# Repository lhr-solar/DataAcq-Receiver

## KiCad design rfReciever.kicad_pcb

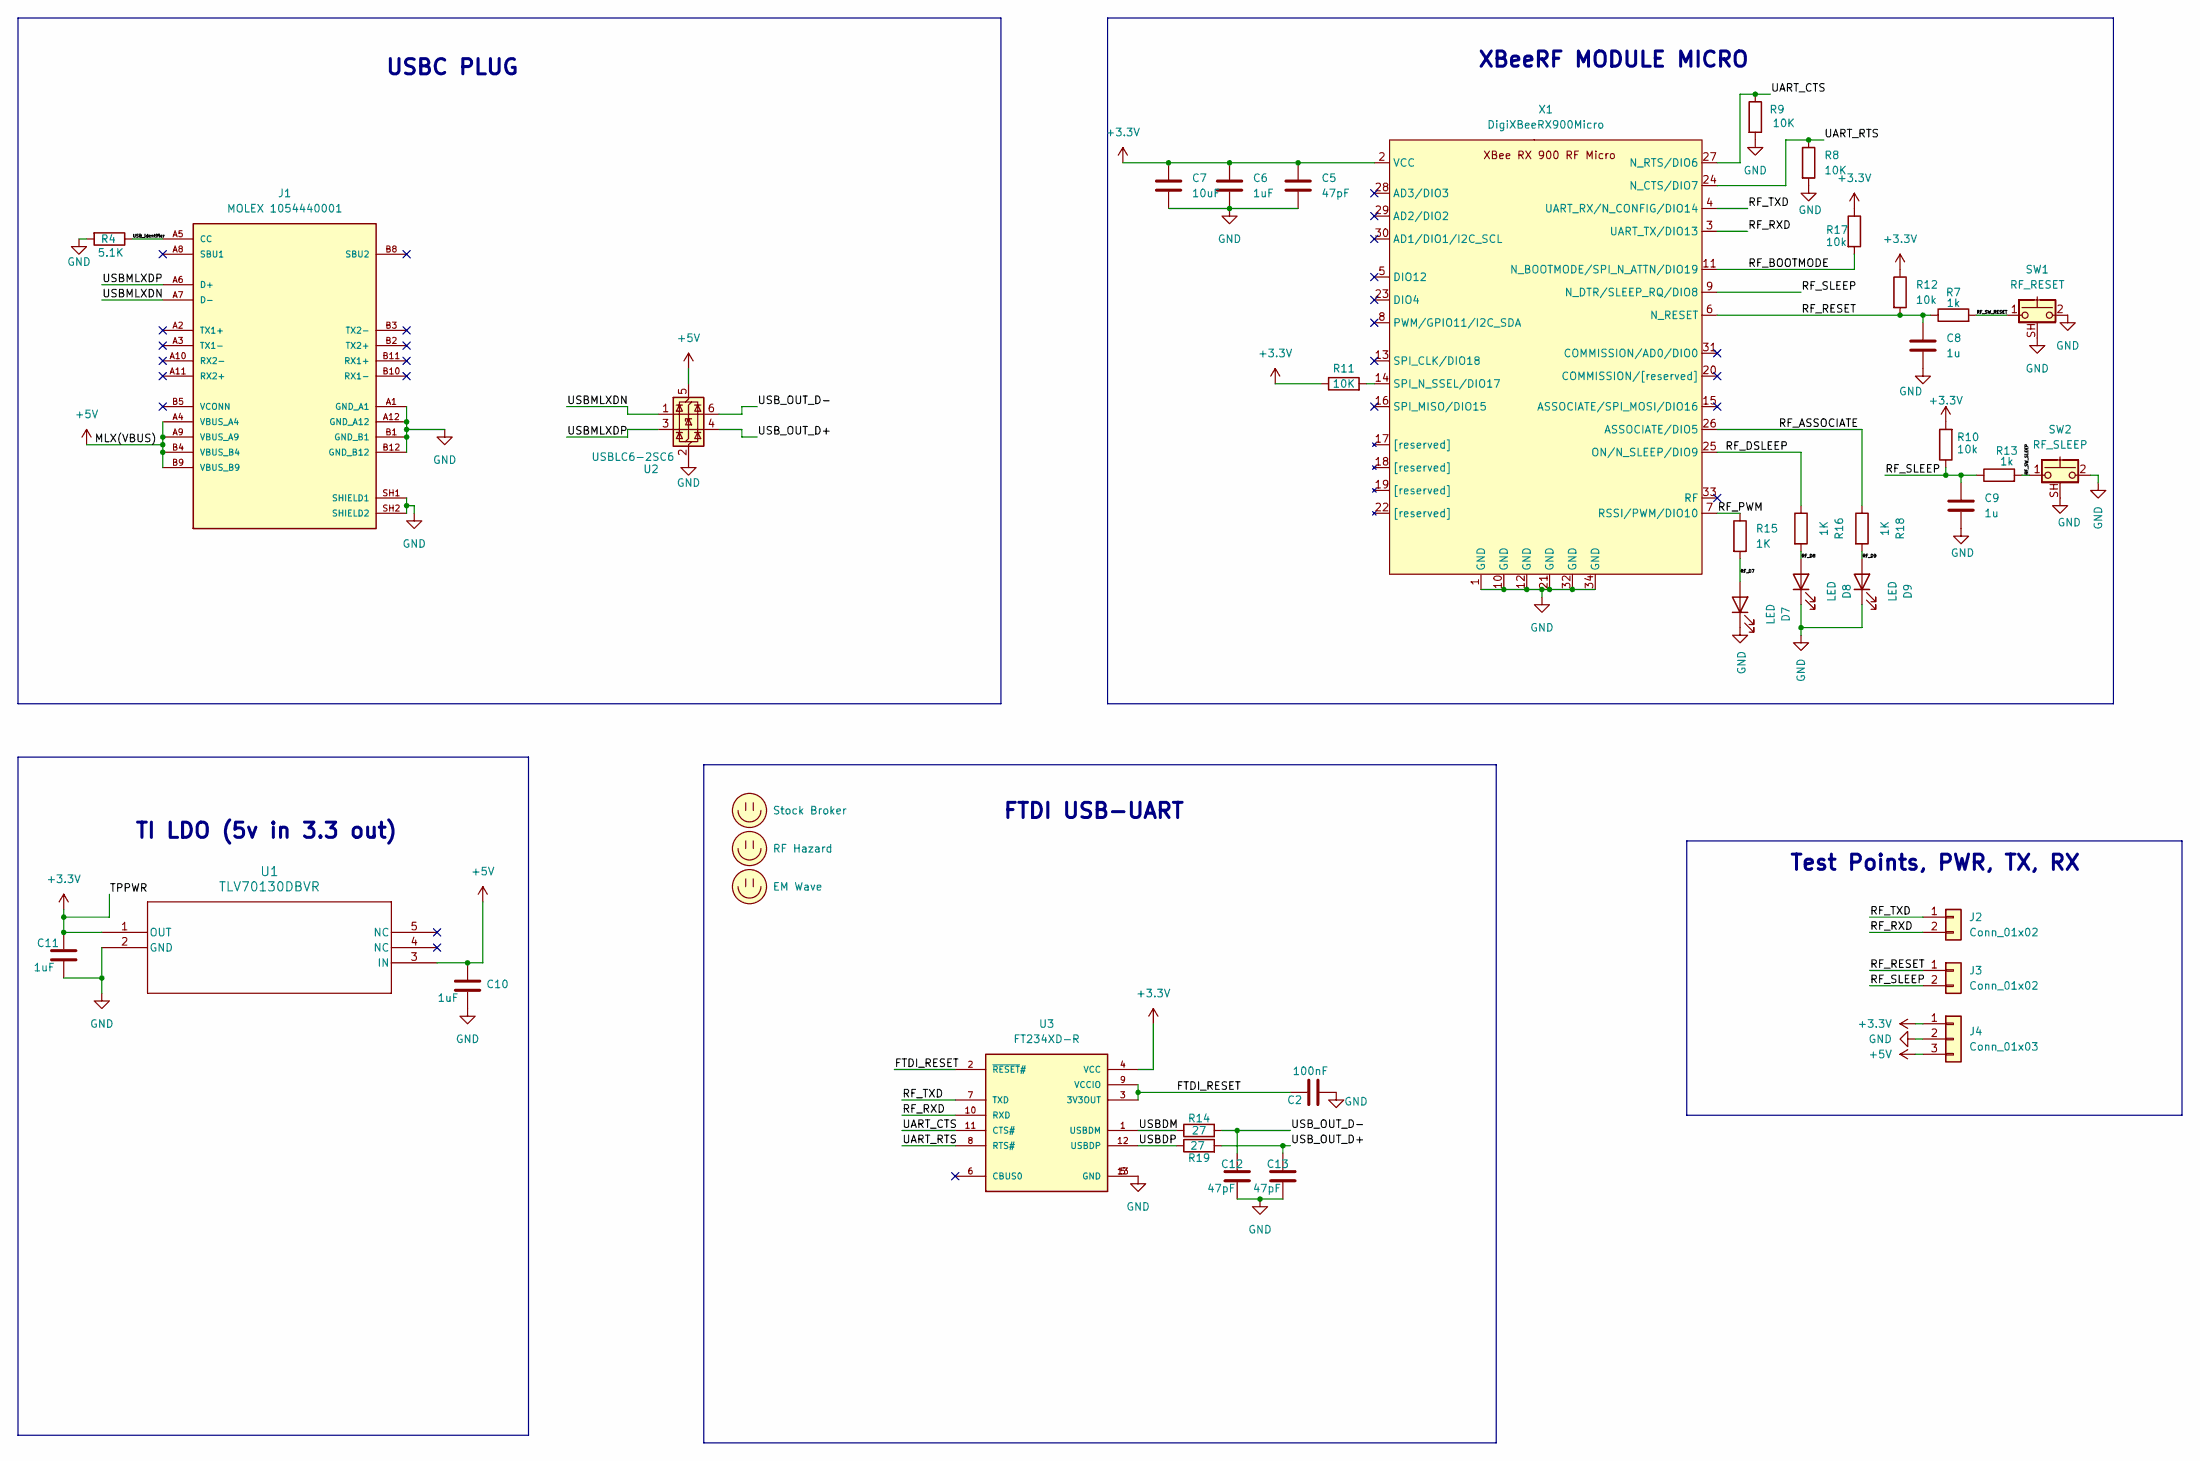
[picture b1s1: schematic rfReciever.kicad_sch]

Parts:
C2: 100nF; C_0805_2012Metric
C5, C12, C13: 47pF; C_0805_2012Metric
C6, C10, C11: 1uF; C_0805_2012Metric
C7: 10uF; C_0805_2012Metric
C8, C9: 1u; C_0805_2012Metric; Mouser Part Number 80-C0805C105J4RACLR
D7, D8, D9: LED; LED_0805_2012Metric
J1: MOLEX 1054440001; MOLEX_1054440001; PARTREV C2
J2, J3: Conn_01x02; PinHeader_1x02_P2.00mm_Vertical_SMD_Pin1Left
J4: Conn_01x03; PinHeader_1x03_P2.54mm_Vertical
LOGO1: Stock Broker; stockBroker
LOGO2: RF Hazard; RFHazard
LOGO3: EM Wave; emWave
R4: 5.1K; R_0805_2012Metric
R7, R13: 1k; R_0805_2012Metric; Mouser Part Number 71-CRCW08051K00FKEAC
R8, R9, R11: 10K; R_0805_2012Metric
R10, R12, R17: 10k; R_0805_2012Metric
R14, R19: 27; R_0805_2012Metric
R15, R16, R18: 1K; R_0805_2012Metric
SW1: RF_RESET; SW_SPST_CK_KMS2xxGP
SW2: RF_SLEEP; SW_SPST_CK_KMS2xxGP
U1: TLV70130DBVR; DBV5
U2: USBLC6-2SC6; SOT-23-6
U3: FT234XD-R; SON45P300X300X80-13N; PARTREV Version 1.2
X1: DigiXBeeRX900Micro; XBeeXR900RFMicro

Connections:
+3.3V: C5.1, C6.1, C7.1, C11.1, J4.1, R10.2, R11.1, R12.1, R17.1, U1.1 (OUT), U3.4 (VCC), X1.2 (VCC)
+5V: C10.1, J1.A4 (VBUS_A4), J1.A9 (VBUS_A9), J1.B4 (VBUS_B4), J1.B9 (VBUS_B9), J4.3, U1.3 (IN), U2.5 (VBUS)
/FTDI_RESET: C2.1, U3.2 (~RESET#), U3.3 (3V3OUT), U3.9 (VCCIO)
/RF_ASSOCIATE: R18.1, X1.26 (ASSOCIATE/DIO5)
/RF_BOOTMODE: R17.2, X1.11 (N_BOOTMODE/SPI_N_ATTN/DIO19)
/RF_D7: D7.2 (A), R15.2
/RF_D8: D8.2 (A), R16.2
/RF_D9: D9.2 (A), R18.2
/RF_DSLEEP: R16.1, X1.25 (ON/N_SLEEP/DIO9)
/RF_PWM: R15.1, X1.7 (RSSI/PWM/DIO10)
/RF_RESET: C8.1, J3.1, R7.1, R12.2, X1.6 (N_RESET)
/RF_RXD: J2.2, U3.10 (RXD), X1.3 (UART_TX/DIO13)
/RF_SLEEP: C9.1, J3.2, R10.1, R13.1, X1.9 (N_DTR/SLEEP_RQ/DIO8)
/RF_SW_RESET: R7.2, SW1.1
/RF_SW_SLEEP: R13.2, SW2.1
/RF_TXD: J2.1, U3.7 (TXD), X1.4 (UART_RX/N_CONFIG/DIO14)
/UART_CTS: R9.1, U3.11 (CTS#), X1.27 (N_RTS/DIO6)
/UART_RTS: R8.1, U3.8 (RTS#), X1.24 (N_CTS/DIO7)
/USBDM: R14.1, U3.1 (USBDM)
/USBDP: R19.1, U3.12 (USBDP)
/USBMLXDN: J1.A7 (D-), U2.1 (I/O1)
/USBMLXDP: J1.A6 (D+), U2.3 (I/O2)
/USB_Identifier: J1.A5 (CC), R4.1
/USB_OUT_D+: C13.1, R19.2, U2.4 (I/O2)
/USB_OUT_D-: C12.1, R14.2, U2.6 (I/O1)
GND: C2.2, C5.2, C6.2, C7.2, C8.2, C9.2, C10.2, C11.2, C12.2, C13.2, D7.1 (K), D8.1 (K), D9.1 (K), J1.A1 (GND_A1), J1.A12 (GND_A12), J1.B1 (GND_B1), J1.B12 (GND_B12), J1.SH1 (SHIELD1), J1.SH2 (SHIELD2), J4.2, R4.2, R8.2, R9.2, SW1.2, SW1.SH (B), SW2.2, SW2.SH (B), U1.2 (GND), U2.2 (GND), U3.5 (GND), U3.13 (GND), X1.1 (GND), X1.10 (GND), X1.12 (GND), X1.21 (GND), X1.32 (GND), X1.34 (GND)
unnamed: R11.2, X1.14 (SPI_N_SSEL/DIO17)

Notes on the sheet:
FTDI USB-UART
Test Points, PWR, TX, RX
TI LDO (5v in 3.3 out)
XBeeRF MODULE MICRO
USBC PLUG

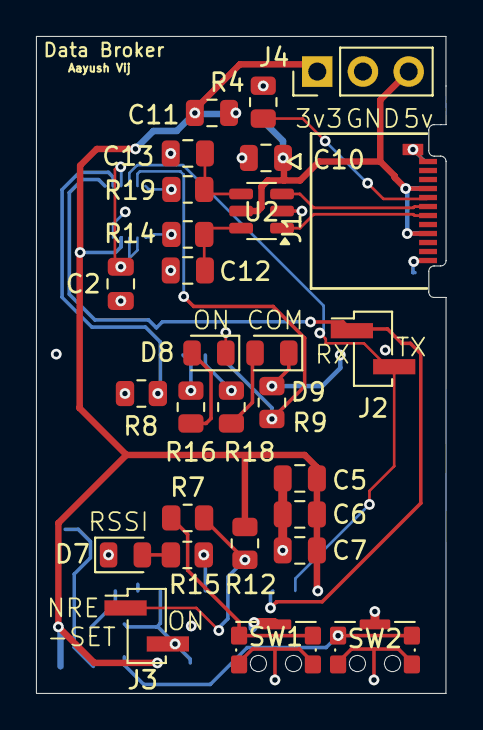
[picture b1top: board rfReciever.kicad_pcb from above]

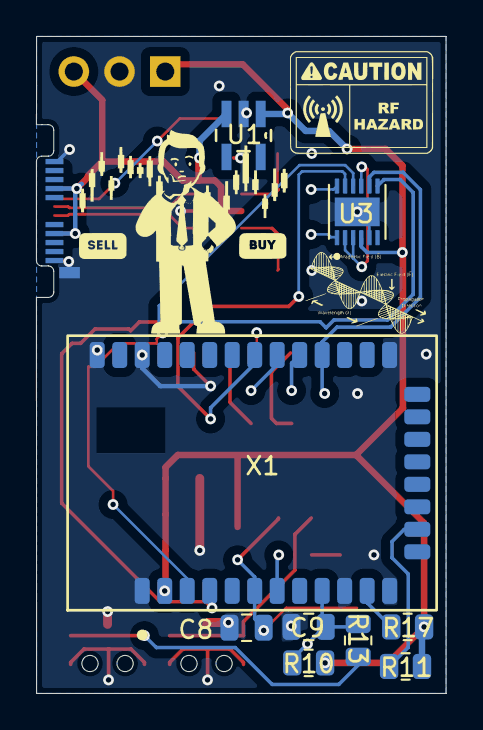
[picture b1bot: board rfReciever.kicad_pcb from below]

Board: 4 copper layers, 22.8 x 36.5 mm, 40 parts (12 on the bottom side), 27 nets.

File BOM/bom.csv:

Reference,Value,Datasheet,Footprint,Qty,Mouser Part Number
C2,100nF,~,Capacitor_SMD:C_0805_2012Metric,1,80-C0805R104J5RACTU
"C5,C12,C13",47pF,~,Capacitor_SMD:C_0805_2012Metric,3,80-C0805C470F5G
"C6,C10,C11",1uF,~,Capacitor_SMD:C_0805_2012Metric,3,75-F17725102900
C7,10uF,~,Capacitor_SMD:C_0805_2012Metric,1,810-C1608X7T1A106M08
"C8,C9",1uF,~,Capacitor_SMD:C_0805_2012Metric,2,75-F17725102900
"D7,D8,D9",LED,~,LED_SMD:LED_0805_2012Metric,3,941-XPLDCL00HC6AAAE7
J1,MOLEX 1054440001,https://www.molex.com/en-us/products/part-detail-pdf/1054440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,rfReciever-Footprints:MOLEX_1054440001,1,538-105444-0001
J2,Conn_01x03,~,Connector_PinHeader_2.54mm:PinHeader_1x03_P2.54mm_Vertical,1,538-22-28-4035 
R4,5.1K,~,Resistor_SMD:R_0805_2012Metric,1,"71-TNPU06035K10AYEN0	"
"R7,R13",1k,~,Resistor_SMD:R_0805_2012Metric,2,71-CRCW08051K00FKEAC
"R8,R9,R11",10K,~,Resistor_SMD:R_0805_2012Metric,3,71-CRCW080510K0FKEAC
"R10,R12,R17",10k,~,Resistor_SMD:R_0805_2012Metric,3,71-CRCW080510K0FKEAC
"R14,R19",27,~,Resistor_SMD:R_0805_2012Metric,2,594-MCU08050C2709FP5
"R15,R16,R18",1K,~,Resistor_SMD:R_0805_2012Metric,3,71-CRCW08051K00FKEAC
SW1,RF_RESET,https://www.ckswitches.com/media/1482/kms.pdf,Button_Switch_SMD:SW_SPST_CK_KMS2xxGP,1,611-KMS231GLFS
SW2,RF_SLEEP,https://www.ckswitches.com/media/1482/kms.pdf,Button_Switch_SMD:SW_SPST_CK_KMS2xxGP,1,611-KMS231GLFS
U1,TLV70130DBVR,TLV70130DBVR,rfReciever-Footprints:DBV5,1,595-TLV70130DBVR
U2,USBLC6-2SC6,https://www.st.com/resource/en/datasheet/usblc6-2.pdf,Package_TO_SOT_SMD:SOT-23-6,1,511-USBLC6-2SC6
U3,FT234XD-R,https://www.ftdichip.com/Support/Documents/DataSheets/ICs/DS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,rfReciever-Footprints:SON45P300X300X80-13N,1,895-FT234XD-R
X1,DigiXBeeRX900Micro,https://fcc.report/FCC-ID/MCQ-XB9XR/7222310.pdf,rfReciever-Footprints:XBeeXR900RFMicro,1,~

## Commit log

2025-01-18 double schematic about to fix
2025-01-18 Final Schematic preliminary pcb layout(pre-routing)
2025-01-25 Routing V1, possibly not DRC compliant
2025-01-25 Reworked schematic, partial layout
2025-01-25 layout+routing v2, TODO: rework USB routing
2025-01-27 V3 layout TODO: Rework to be 4 layer board
2025-02-01 4 layer layout, new esd protection for USB
2025-02-01 Fixed up layout + shematic
2025-02-05 new molex connector, final layout
2025-02-09 3d models + ground vias + new usbc
2025-02-14 BOM with mouser part #
2025-02-15 update molex footprint, start working through DRC
2025-02-15 fixed usbc misaligned
2025-02-15 fixed edge cuts
2025-02-15 fixed traces and errors
2025-02-22 updated schematic with new bridge and LDO (label "VCCIO" (at 228.6 199.39 0) (fields_autoplaced yes) (effects (font (size 1.27 1.27)) (justify left bottom)) (uuid "1f50f597-85ab-42bc-9a9f-0ec370d6b6a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
2025-03-01 reworked schematic v1 matthew review
2025-03-01 all datasheets pushed
2025-03-01 schematic mk2 post matthew review
2025-03-01 gitignore + layout v3 + routing
2025-03-08 revisions requested by Lakshay, new LDO
2025-03-08 removed lock files
2025-03-08 removed all lck files
2025-03-24 reworked layout slightly + 3d models
2025-03-25 added testpoints, TODO: Ground pours + ground conn
2025-03-25 ground pours + ground vias
2025-03-25 fix unconnected errors, 1 real error left?
2025-03-27 update BOM
2025-05-17 Minor updates (test points, silkscreen, traces)
2025-05-19 More minor tweaks + silkscreen
2025-05-19 fixed drc
